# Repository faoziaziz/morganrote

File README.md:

# morganrote
# morganrote

# Revision Notes

v0.1
---
1. Use default of sdr source from AD9009

v0.2
1. Trying to cost down of the device

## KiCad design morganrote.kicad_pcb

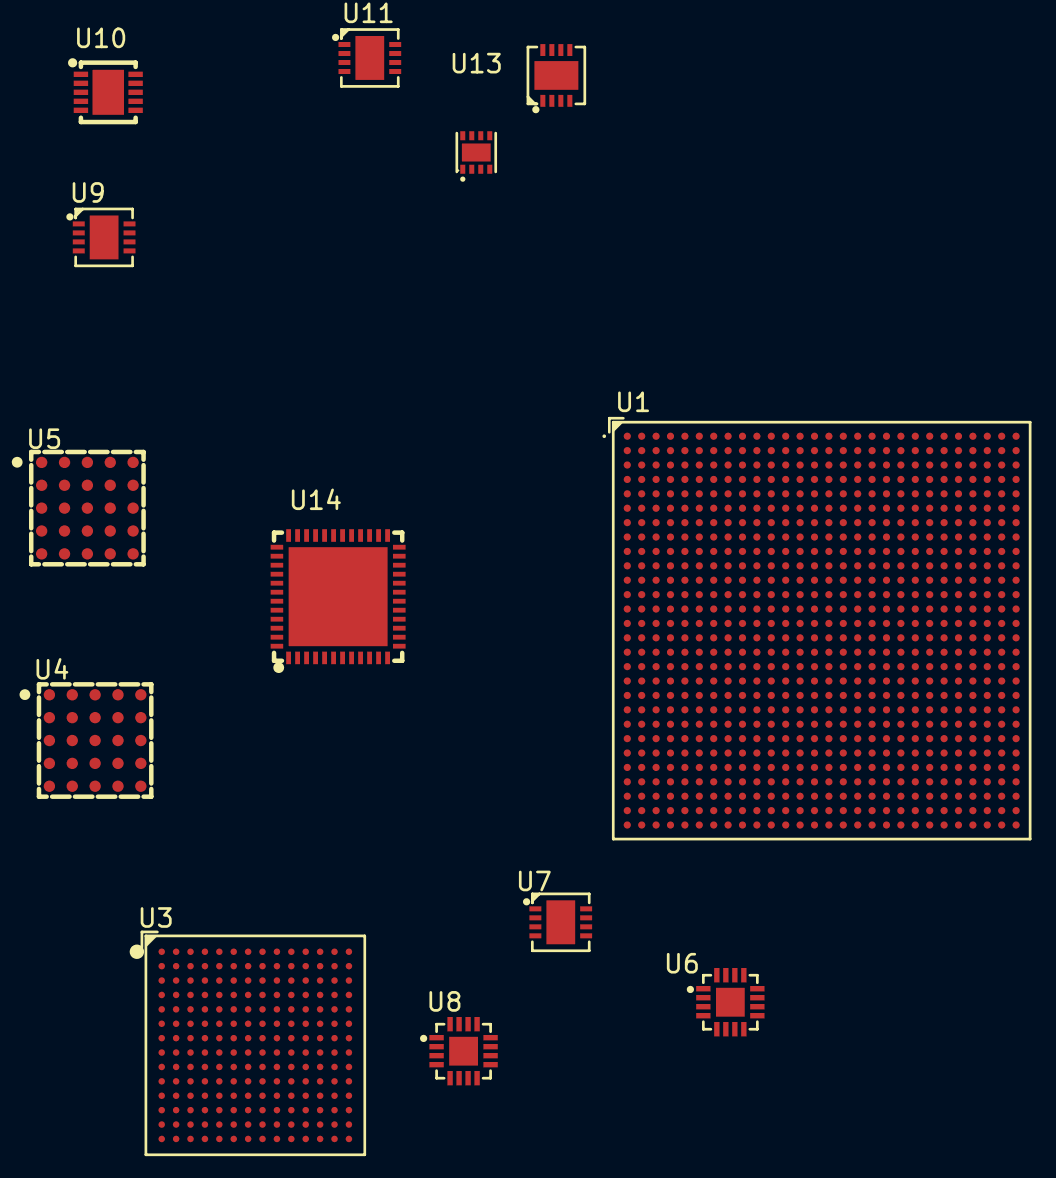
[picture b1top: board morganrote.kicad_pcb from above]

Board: 2 copper layers, 13 parts (0 on the bottom side), 33 nets, no tracks yet.

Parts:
U1: XCZU3EG-2SFVC784E; FCBGA-784_L23.0-W23.0-R28-C28-P0.80-BL
U3: ADRV9009BBCZ; CSPBGA-196_L12.0-W12.0-R14-C14-P0.80-TL
U4, U5: LTM4632IY; BGA-25_L6.3-W6.3-R5-C5-P1.27-BL
U6, U8: ADP1763ACPZ-1.3; LFCSP-16_L3.0-W3.0-P0.50-TL-EP1.6
U7, U9: ADM7154ACPZ-1.8; LFCSP-8_L3.0-W3.0-P0.50-BL-EP
U10: ADP7158ACPZ-3.3-R7; LFCSP-10_L3.0-W3.0-P0.50-BL-EP
U11, U12: ADM7154ACPZ-3.3; LFCSP-8_L3.0-W3.0-P0.50-BL-EP
U13: ADP124ACPZ-3.3; LFCSP-8_L2.0-W2.0-P0.50-BL-EP
U14: ADP5054ACPZ; LFCSP-48_L7.0-W7.0-P0.50-BL-EP5.5-A

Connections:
1V2_PL_DDR4: U5.D1 (VOUT1), U5.E1 (VOUT1)
1V2_PS_DDR4: U4.A4 (VDDQIN), U4.D1 (VOUT1), U4.E1 (VOUT1), U5.A4 (VDDQIN)
12V0: U4.A2 (VIN), U4.B3 (VIN), U4.D3 (VIN), U4.E2 (VIN), U5.A2 (VIN), U5.B3 (VIN), U5.D3 (VIN), U5.E2 (VIN), U14.6 (PVIN3), U14.7 (PVIN4), U14.22 (PVIN2), U14.23 (PVIN2), U14.24 (PVIN2), U14.36 (PVIN1), U14.37 (PVIN1), U14.38 (PVIN1)
/MPSoC/ddr_supply/EN_1V2_DDR4: U4.B2 (RUN2), U4.D2 (RUN1), U5.B2 (RUN2), U5.D2 (RUN1)
/MPSoC/ddr_supply/PG_DDR4: U4.B4 (PGOOD2), U4.D4 (PGOOD1), U5.B4 (PGOOD2), U5.D4 (PGOOD1)
/Power/RF_supply_1/VDDA1P3_ANLG_A: U6.9 (VOUT), U6.10 (VOUT), U6.11 (VOUT), U6.12 (VOUT), U8.9 (VOUT), U8.10 (VOUT), U8.11 (VOUT), U8.12 (VOUT)
/Power/RF_supply_1/VDDA1P3_ANLG_SNS_A: U6.13 (SENSE), U8.13 (SENSE)
/Power/RF_supply_1/VDDA1P65_ANLG_A: U6.1 (VIN), U6.2 (VIN), U6.3 (VIN), U6.4 (VIN), U6.16 (EN), U8.1 (VIN), U8.2 (VIN), U8.3 (VIN), U8.4 (VIN), U8.16 (EN)
/transciever/VDD1P3_DIG_A: U3.L8 (VDDD1P3_DIG), U3.L9 (VDDD1P3_DIG)
/transciever/VDDA1P3_DES_A: U3.N9 (VDDA1O3_DES), U3.P9 (VDDA1P3_DES)
/transciever/VDDA1P3_RF_VCO_LDO_A: U3.C5 (VDDA1P3_RF_VCO_LDO), U3.C6 (VDDA1P3_RF_VCO_LDO)
/transciever/VDDA1P3_SER_A: U3.N8 (VDDA1P3_SER), U3.P8 (VDDA1P3_SER)
GNDREF: U1.A20 (GND), U1.A24 (GND), U1.A27 (GND), U1.A28 (GND), U1.AA1 (GND), U1.AA2 (GND), U1.AA3 (GND), U1.AA4 (GND), U1.AA5 (GND), U1.AA6 (GND), U1.AA9 (GND), U1.AA19 (GND), U1.AA24 (GND), U1.AB12 (GND), U1.AB27 (GND), U1.AC15 (GND), U1.AC20 (GND), U1.AC25 (GND), U1.AD3 (GND), U1.AD18 (GND), U1.AE1 (GND), U1.AE6 (GND), U1.AE11 (GND), U1.AE21 (GND), U1.AE26 (GND), U1.AF4 (GND), U1.AF9 (GND), U1.AF14 (GND), U1.AF19 (GND), U1.AG2 (GND), U1.AG22 (GND), U1.AG27 (GND), U1.AH5 (GND), U1.B2 (GND), U1.B21 (GND), U1.B25 (GND), U1.B26 (GND), U1.C5 (GND), U1.C10 (GND), U1.C20 (GND), U1.C24 (GND), U1.C27 (GND), U1.C28 (GND), U1.D8 (GND), U1.D13 (GND), U1.D21 (GND), U1.D26 (GND), U1.E16 (GND), U1.E20 (GND), U1.E24 (GND), U1.E27 (GND), U1.E28 (GND), U1.F4 (GND), U1.F9 (GND), U1.F19 (GND), U1.F21 (GND), U1.F25 (GND), U1.F26 (GND), U1.G2 (GND), U1.G7 (GND), U1.G12 (GND), U1.G22 (GND), U1.G23 (GND), U1.G24 (GND), U1.G27 (GND), U1.G28 (GND), U1.H10 (GND), U1.H15 (GND), U1.H25 (GND), U1.J8 (GND), U1.J13 (GND), U1.J18 (GND), U1.J23 (GND), U1.K6 (GND), U1.K11 (GND), U1.K16 (GND), U1.K21 (GND), U1.K26 (GND), U1.L9 (GND), U1.L24 (GND), U1.M1 (GND), U1.M2 (GND), U1.M3 (GND), U1.M4 (GND), U1.M5 (GND), U1.M7 (GND), U1.M22 (GND), U1.M27 (GND), U1.N5 (GND), U1.N10 (GND), U1.N12 (GND), U1.N14 (GND), U1.N20 (GND), U1.N25 (GND), U1.P3 (GND), U1.P5 (GND), U1.P8 (GND), U1.P11 (GND), U1.R1 (GND), U1.R2 (GND), U1.R5 (GND), U1.R15 (GND), U1.R21 (GND), U1.R26 (GND), U1.T3 (GND), U1.T5 (GND), U1.T9 (GND), U1.T10 (GND), U1.T14 (GND), U1.T19 (GND), U1.U1 (GND), U1.U2 (GND), U1.U6 (GND), U1.U11 (GND), U1.U17 (GND), U1.U21 (RSVDGND), U1.U22 (GND), U1.U27 (GND), U1.V3 (GND), U1.V7 (GND), U1.V13 (GND), U1.V15 (GND), U1.V20 (RSVDGND), U1.V21 (RSVDGND), U1.W1 (GND), U1.W2 (GND), U1.W6 (GND), U1.W18 (GND), U1.W21 (RSVDGND), U1.W23 (GND), U1.Y3 (GND), U1.Y7 (GND), U1.Y11 (GND), U1.Y16 (GND), U1.Y21 (RSVDGND), U3.A1 (VSSA), U3.A4 (VSSA), U3.A7 (VSSA), U3.A8 (VSSA), U3.A11 (VSSA), U3.A14 (VSSA), U3.B2 (VSSA), U3.B3 (VSSA), U3.B4 (VSSA), U3.B5 (VSSA), U3.B6 (VSSA), U3.B9 (VSSA), U3.B10 (VSSA), U3.B11 (VSSA), U3.B12 (VSSA), U3.B13 (VSSA), U3.B14 (VSSA), U3.C4 (VSSA), U3.C9 (VSSA), U3.C11 (VSSA), U3.D3 (VSSA), U3.D4 (VSSA), U3.D5 (VSSA), U3.D6 (VSSA), U3.D7 (VSSA), U3.D8 (VSSA), U3.D9 (VSSA), U3.D11 (VSSA), U3.D12 (VSSA), U3.E6 (VSSA), U3.E9 (VSSA), U3.F1 (VSSA), U3.F2 (VSSA), U3.F5 (VSSA), U3.F6 (VSSA), U3.F7 (VSSA), U3.F8 (VSSA), U3.F9 (VSSA), U3.F10 (VSSA), U3.F12 (VSSA), U3.F13 (VSSA), U3.F14 (VSSA), U3.G1 (VSSA), U3.G2 (VSSA), U3.G3 (VSSA), U3.G4 (VSSA), U3.G6 (VSSA), U3.G10 (VSSA), U3.G11 (VSSA), U3.G12 (VSSA), U3.G13 (VSSA), U3.G14 (VSSA), U3.H2 (VSSA), U3.H3 (VSSA), U3.H4 (VSSA), U3.H5 (VSSA), U3.H6 (VSSA), U3.H7 (VSSA), U3.H8 (VSSA), U3.H9 (VSSA), U3.H10 (VSSA), U3.H13 (VSSA), U3.J2 (VSSA), U3.J13 (VSSA), U3.K1 (VSSA), U3.K2 (VSSA), U3.K13 (VSSA), U3.K14 (VSSA), U3.L1 (VSSA), U3.L2 (VSSA), U3.L7 (VSSD), U3.L10 (VSSD), U3.M2 (VSSA), U3.M9 (VSSA), U3.N2 (VSSA), U3.N7 (VSSA), U3.N14 (VSSA), U3.P2 (VSSA), U3.P3 (VSSA), U3.P10 (VSSA), U4.B5 (GND), U4.C1 (GND), U4.C2 (GND), U4.C4 (GND), U4.C5 (SYNC/MODE), U4.D5 (GND), U5.B5 (GND), U5.C1 (GND), U5.C2 (GND), U5.C4 (GND), U5.C5 (SYNC/MODE), U5.D5 (GND), U6.7 (GND), U7.4 (GND), U8.7 (GND), U9.4 (GND), U10.11 (EP), U11.0 (EP), U11.4 (GND), U12.0 (EP), U12.4 (GND), U13.4 (GND), U14.2 (PGND3), U14.3 (PGND3), U14.10 (PGND4), U14.11 (PGND4), U14.30 (PGND), U14.49 (EPAD)
unnamed: U14.8 (SW4), U14.9 (SW4)
unnamed: U14.4 (SW3), U14.5 (SW3)
unnamed: U14.33 (SW1), U14.34 (SW1), U14.35 (SW1)
unnamed: U14.25 (SW2), U14.26 (SW2), U14.27 (SW2)
unnamed: U11.7 (EN), U11.8 (VIN)
unnamed: U12.7 (EN), U12.8 (VIN)
unnamed: U14.14 (EN4), U14.48 (EN3)
VCCp0V85: U1.AA15 (VCC_PSINTFP), U1.AA16 (VCC_PSINTFP), U1.AA17 (VCC_PSINTFP), U1.AA18 (VCC_PSINTFP), U1.AA20 (VCC_PSINTFP_DDR), U1.AA21 (VCC_PSINTFP_DDR), U1.AB16 (VCC_PSINTFP), U1.K10 (VCCINT_IO), U1.L10 (VCCINT_IO), U1.L11 (VCCBRAM), U1.L12 (VCCBRAM), U1.M9 (VCCINT_IO), U1.M10 (VCCINT_IO), U1.M11 (VCCBRAM), U1.M12 (VCCBRAM), U1.N11 (VCCINT), U1.N13 (VCCINT), U1.N15 (VCCINT), U1.P10 (VCCINT), U1.P14 (VCCINT), U1.P15 (VCCINT), U1.R10 (VCCINT), U1.R11 (VCCINT), U1.R14 (VCCINT), U1.T11 (VCCINT), U1.T15 (VCCINT), U1.U10 (VCCINT), U1.U14 (VCCINT), U1.U15 (VCCINT), U1.V10 (VCCINT), U1.V11 (VCCINT), U1.V12 (VCCINT), U1.V14 (VCCINT), U1.V16 (VCC_PSINTLP), U1.V17 (VCC_PSINTLP), U1.V18 (VCC_PSINTLP), U1.W15 (VCC_PSINTLP), U1.W16 (VCC_PSINTLP), U1.W17 (VCC_PSINTLP), U1.Y15 (VCC_PSINTFP), U1.Y17 (VCC_PSINTFP), U1.Y19 (VCC_PSINTFP_DDR)
VCCp1V2: U1.AB22 (VCCO_PSDDR_504), U1.AD23 (VCCO_PSDDR_504), U1.AF24 (VCCO_PSDDR_504), U1.P23 (VCCO_PSDDR_504), U1.T24 (VCCO_PSDDR_504), U1.V25 (VCCO_PSDDR_504), U1.Y26 (VCCO_PSDDR_504)
VCCp1V2_MGT_AVTT: U1.T16 (VCC_PSPLL), U1.T17 (VCC_PSPLL), U1.T18 (VCC_PSPLL)
VCCp1V8: U1.M13 (VCCAUX_IO), U1.M14 (VCCAUX_IO), U1.M15 (VCCAUX_IO), U1.M16 (VCCAUX), U1.N16 (VCCAUX), U1.U19 (VCC_PSAUX), U1.U20 (VCC_PSAUX), U1.V19 (VCC_PSAUX), U1.W19 (VCC_PSAUX)
VCCp3V3: U1.AC10 (VCCO_44), U1.AG12 (VCCO_44), U1.B12 (VCCO_25), U1.E11 (VCCO_25)
VCCp_GTRAVTT: U1.A23 (PS_MGTRAVTT), U1.C23 (PS_MGTRAVTT), U1.D25 (PS_MGTRAVTT), U1.E23 (PS_MGTRAVTT)
VCCp_GTR_AVCC: U1.B22 (PS_MGTRAVCC), U1.D22 (PS_MGTRAVCC)
VCCp_PSDDRPLL: U1.U16 (VCC_PSDDR_PLL), U1.U18 (VCC_PSDDR_PLL)
VDDA2P65_A: U7.7 (EN), U7.8 (VIN), U9.7 (EN), U9.8 (VIN)
VDDA3P3: U13.1 (VOUT), U13.2 (VOUT), U13.3 (VOUT_SENSE)
VDDA3P3_CLK: U10.1 (VOUT), U10.2 (VOUT), U10.3 (VOUT_SENSE)
VDDA3P8: U10.5 (EN), U10.9 (VIN), U10.10 (VIN), U13.5 (EN), U13.7 (VIN), U13.8 (VIN)
VTT_PS_DDR4: U4.A1 (VOUT2), U4.B1 (VOUT2), U5.A1 (VOUT2), U5.B1 (VOUT2)
